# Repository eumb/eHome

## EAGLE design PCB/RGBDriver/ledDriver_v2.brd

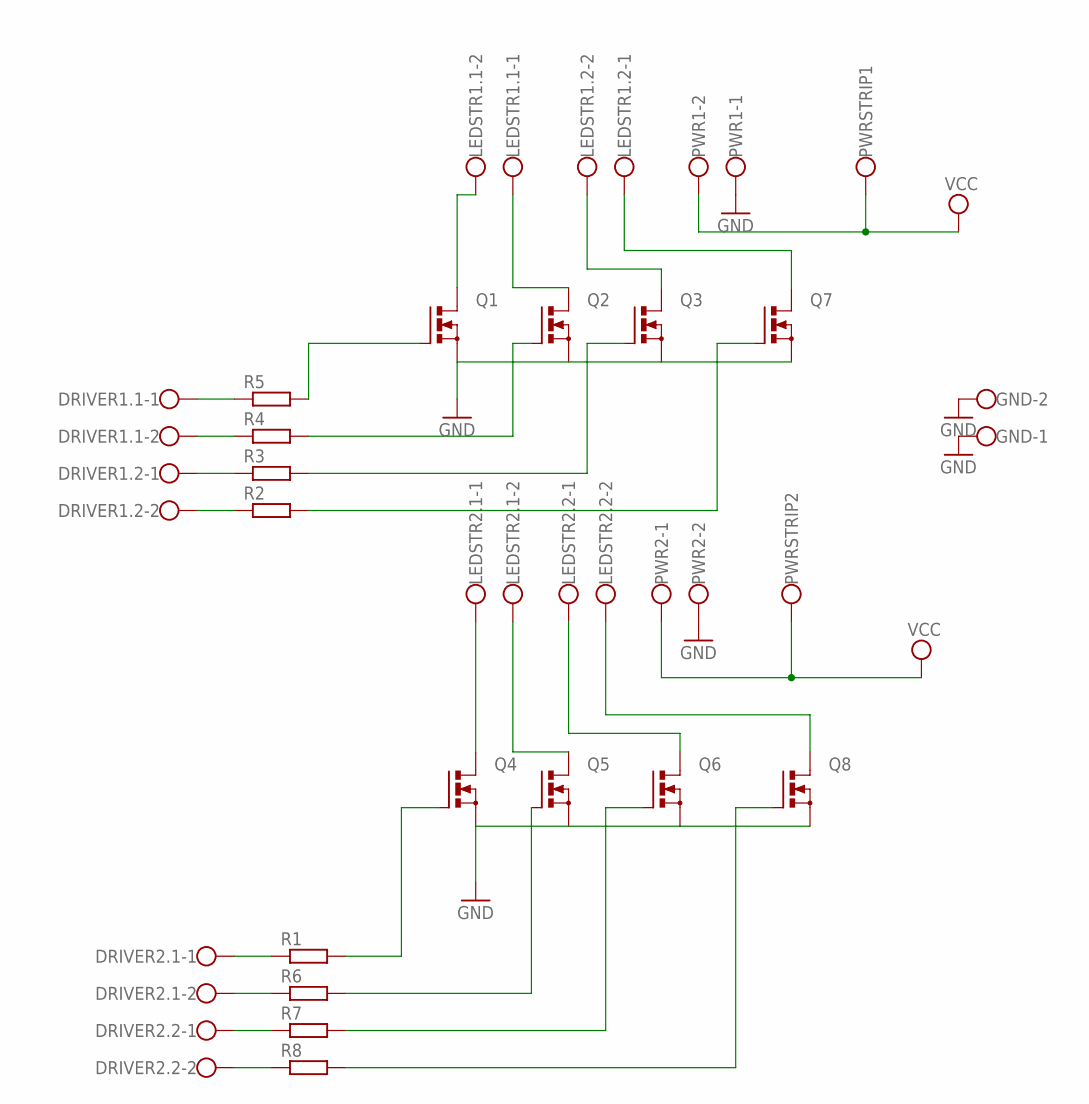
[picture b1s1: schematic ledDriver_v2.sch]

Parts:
DRIVER1.1, DRIVER1.2, DRIVER2.1, DRIVER2.2: W237-102
GND: W237-102
LEDSTR1.1, LEDSTR1.2, LEDSTR2.1, LEDSTR2.2: W237-102
PWR1, PWR2: W237-102
PWRSTRIP1, PWRSTRIP2: W237-112
Q1, Q2, Q3, Q4, Q5, Q6, Q7, Q8: PMOSFET_NTO220BV; TO220BV
R1, R2, R3, R4, R5, R6, R7, R8: R0207/10; 0207/10

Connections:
GND: GND.1, GND.2, PWR1.1, PWR2.2, Q1.S, Q2.S, Q3.S, Q4.S, Q5.S, Q6.S, Q7.S, Q8.S
unnamed: LEDSTR2.1.1, Q4.D
unnamed: LEDSTR2.1.2, Q5.D
unnamed: LEDSTR1.1.2, Q1.D
unnamed: LEDSTR1.1.1, Q2.D
unnamed: LEDSTR1.2.2, Q3.D
unnamed: LEDSTR1.2.1, Q7.D
unnamed: LEDSTR2.2.1, Q6.D
unnamed: LEDSTR2.2.2, Q8.D
unnamed: Q6.G, R7.2
unnamed: Q8.G, R8.2
unnamed: Q1.G, R5.2
unnamed: Q2.G, R4.2
unnamed: Q3.G, R3.2
unnamed: Q7.G, R2.2
unnamed: Q4.G, R1.2
unnamed: Q5.G, R6.2
unnamed: DRIVER1.1.1, R5.1
unnamed: DRIVER1.1.2, R4.1
unnamed: DRIVER1.2.1, R3.1
unnamed: DRIVER1.2.2, R2.1
unnamed: DRIVER2.1.1, R1.1
unnamed: DRIVER2.1.2, R6.1
unnamed: DRIVER2.2.1, R7.1
unnamed: DRIVER2.2.2, R8.1
VCC1: PWR1.2, PWRSTRIP1.1
VCC2: PWR2.1, PWRSTRIP2.1

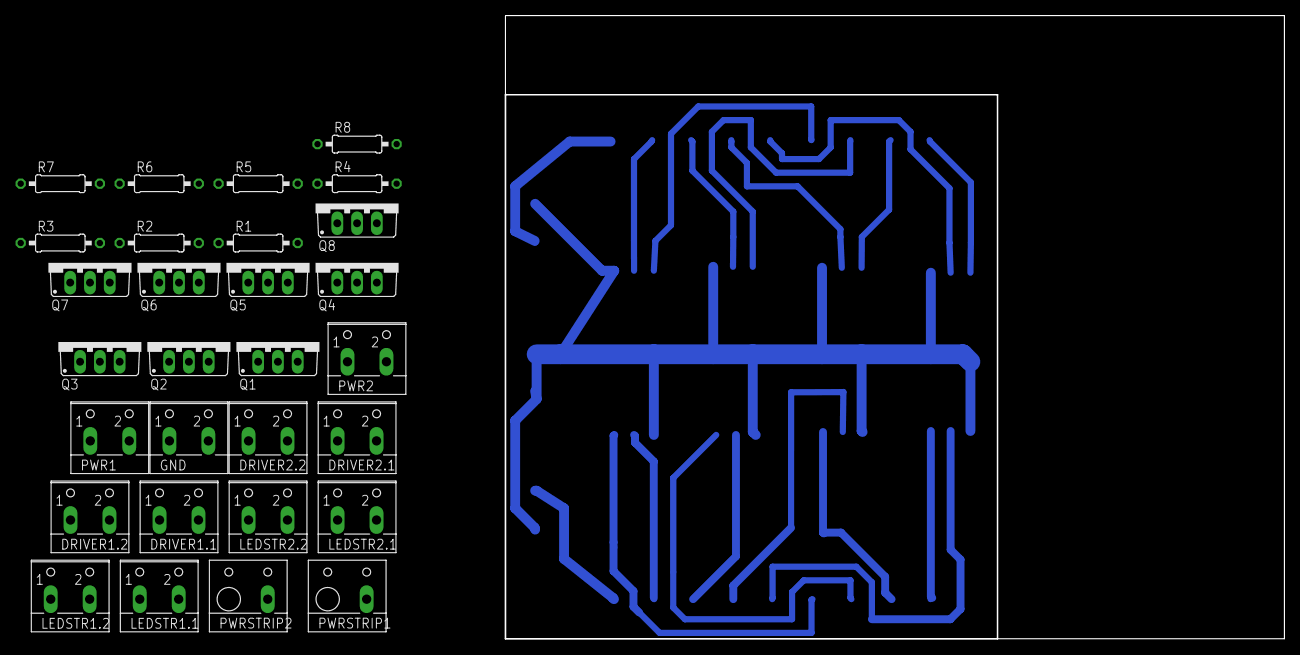
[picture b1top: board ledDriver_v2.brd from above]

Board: 2 copper layers, 100.0 x 80.0 mm, 29 parts (0 on the bottom side), 27 nets.

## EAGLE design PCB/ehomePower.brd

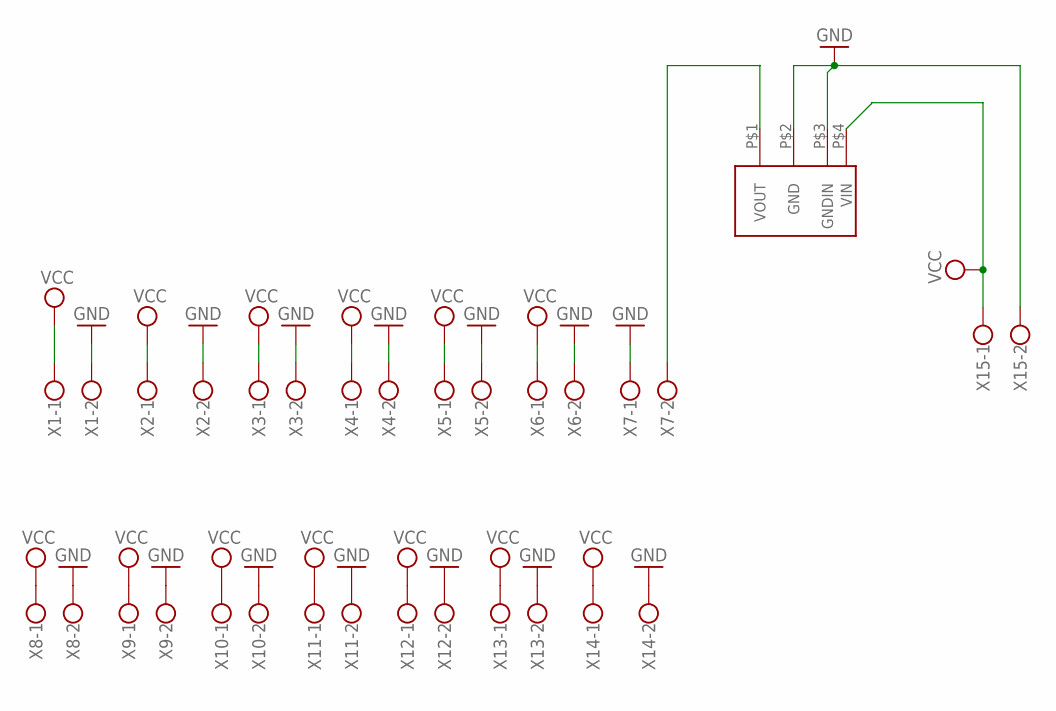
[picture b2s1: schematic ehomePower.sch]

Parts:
U$2: AM2DS
X1, X2, X3, X4, X5, X6, X7, X8, X9, X10, X11, X12, X13, X14, X15: W237-102

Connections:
GND: U$2.P$2 (GND), U$2.P$3 (GNDIN), X1.2, X2.2, X3.2, X4.2, X5.2, X6.2, X7.1, X8.2, X9.2, X10.2, X11.2, X12.2, X13.2, X14.2, X15.2
unnamed: U$2.P$1 (VOUT), X7.2
VCC: U$2.P$4 (VIN), X1.1, X2.1, X3.1, X4.1, X5.1, X6.1, X8.1, X9.1, X10.1, X11.1, X12.1, X13.1, X14.1, X15.1

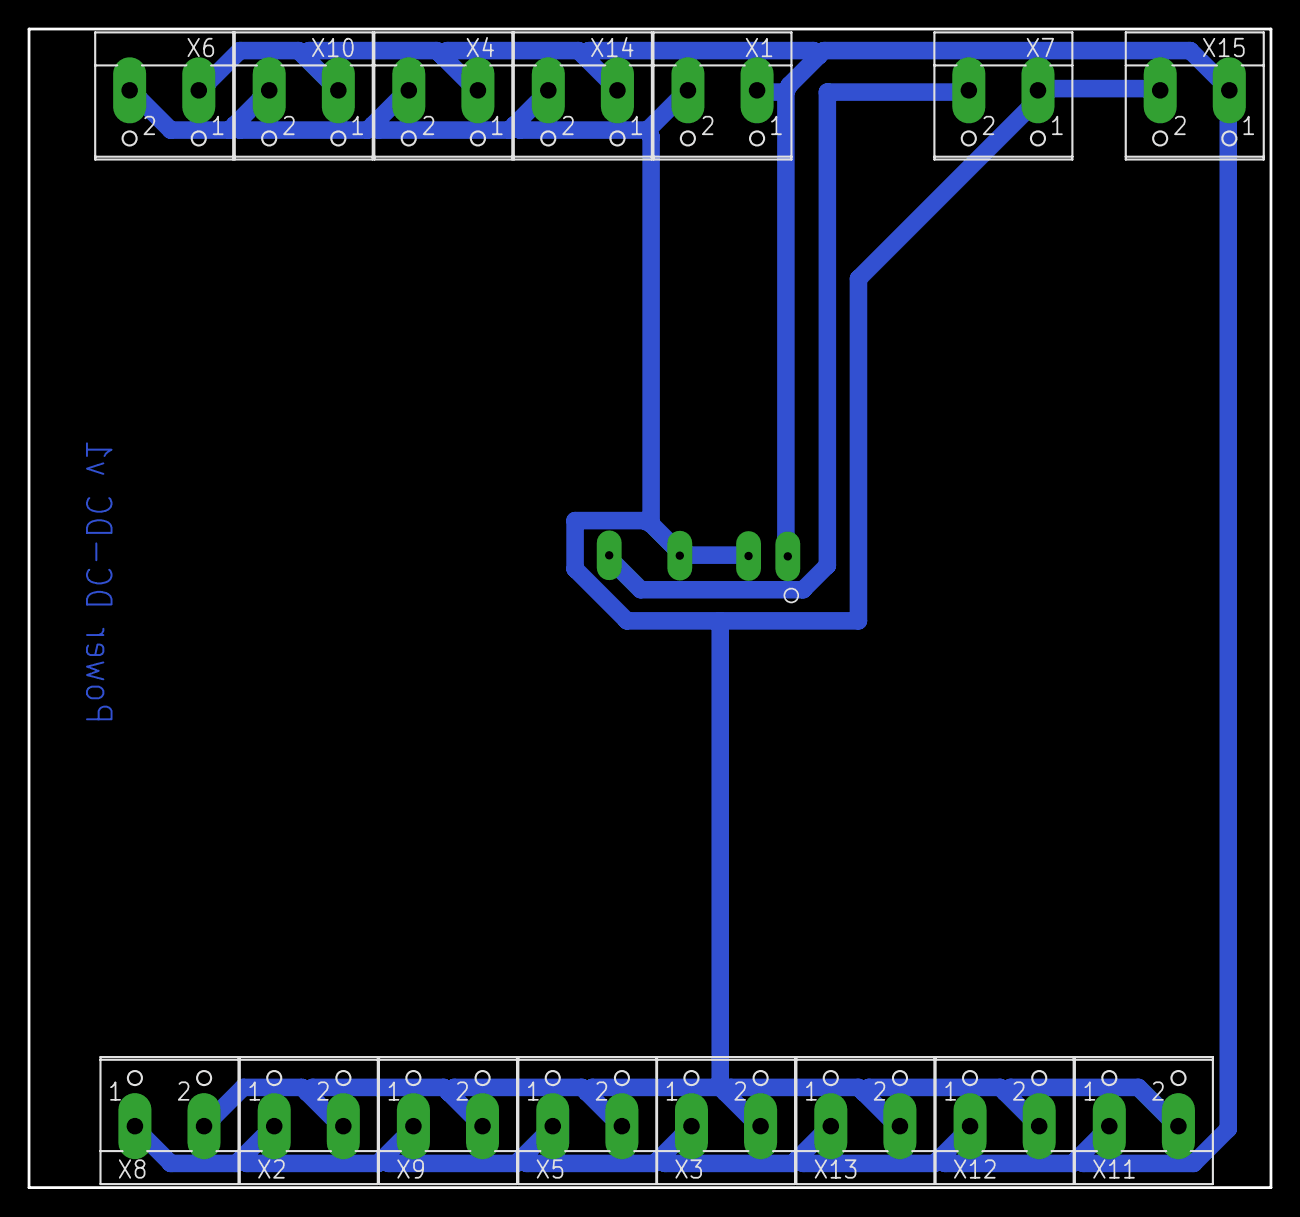
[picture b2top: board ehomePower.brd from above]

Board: 2 copper layers, 89.8 x 83.8 mm, 16 parts (0 on the bottom side), 3 nets.

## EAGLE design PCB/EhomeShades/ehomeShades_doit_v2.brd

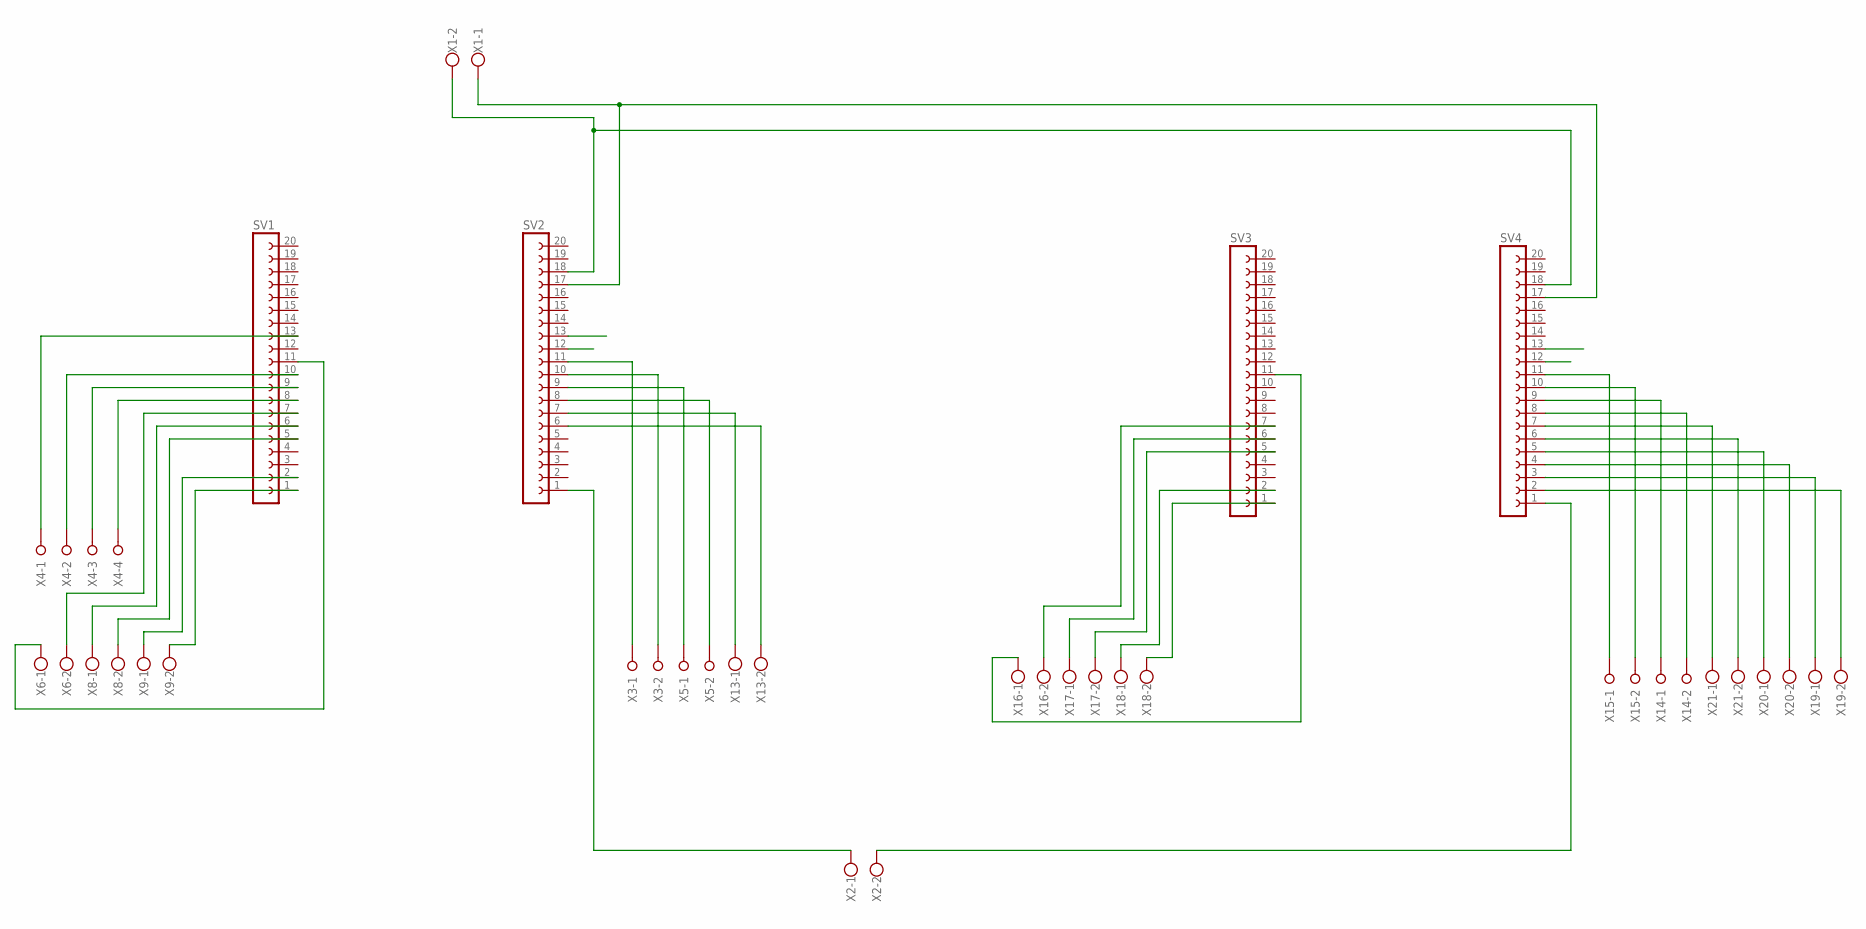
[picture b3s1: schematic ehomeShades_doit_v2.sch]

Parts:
SV1, SV2, SV3, SV4: FE20-1; FE20
X1, X2, X6, X8, X9, X13, X16, X17, X18, X19, X20, X21: W237-102
X3, X5, X14, X15: W237-02P; W237-132
X4: W237-04P; W237-4P

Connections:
EN: SV2.1, X2.1
EN1: SV4.1, X2.2
GND: SV2.17, SV4.17, X1.1
GPIO1: SV4.8, X14.2
GPIO2: SV4.2, X19.2
GPIO3: SV4.3, X19.1
GPIO4: SV1.11, X6.1
GPIO5: SV1.8, X4.4
GPIO6: SV4.4, X20.2
GPIO7: SV4.5, X20.1
GPIO8: SV4.6, X21.2
GPIO9: SV4.7, X21.1
GPIO12: SV2.12
GPIO13: SV2.13
GPIO14: SV2.11, X3.1
GPIO15: SV1.13, X4.1
GPIO16: SV1.10, X4.2
GPIO17: SV1.9, X4.3
GPIO18: SV1.7, X6.2
GPIO19: SV1.6, X8.1
GPIO20: SV3.7, X16.2
GPIO21: SV1.5, X8.2
GPIO22: SV1.2, X9.1
GPIO23: SV1.1, X9.2
GPIO24: SV3.6, X17.1
GPIO25: SV2.8, X5.2
GPIO26: SV2.9, X5.1
GPIO27: SV2.10, X3.2
GPIO28: SV4.9, X14.1
GPIO29: SV4.10, X15.2
GPIO30: SV4.11, X15.1
GPIO31: SV4.13
GPIO32: SV2.6, X13.2
GPIO33: SV2.7, X13.1
GPIO40: SV3.5, X17.2
GPIO41: SV3.2, X18.1
GPIO42: SV3.1, X18.2
GPIO43: SV3.11, X16.1
GPIO44: SV4.12
PWR: SV2.18, SV4.18, X1.2

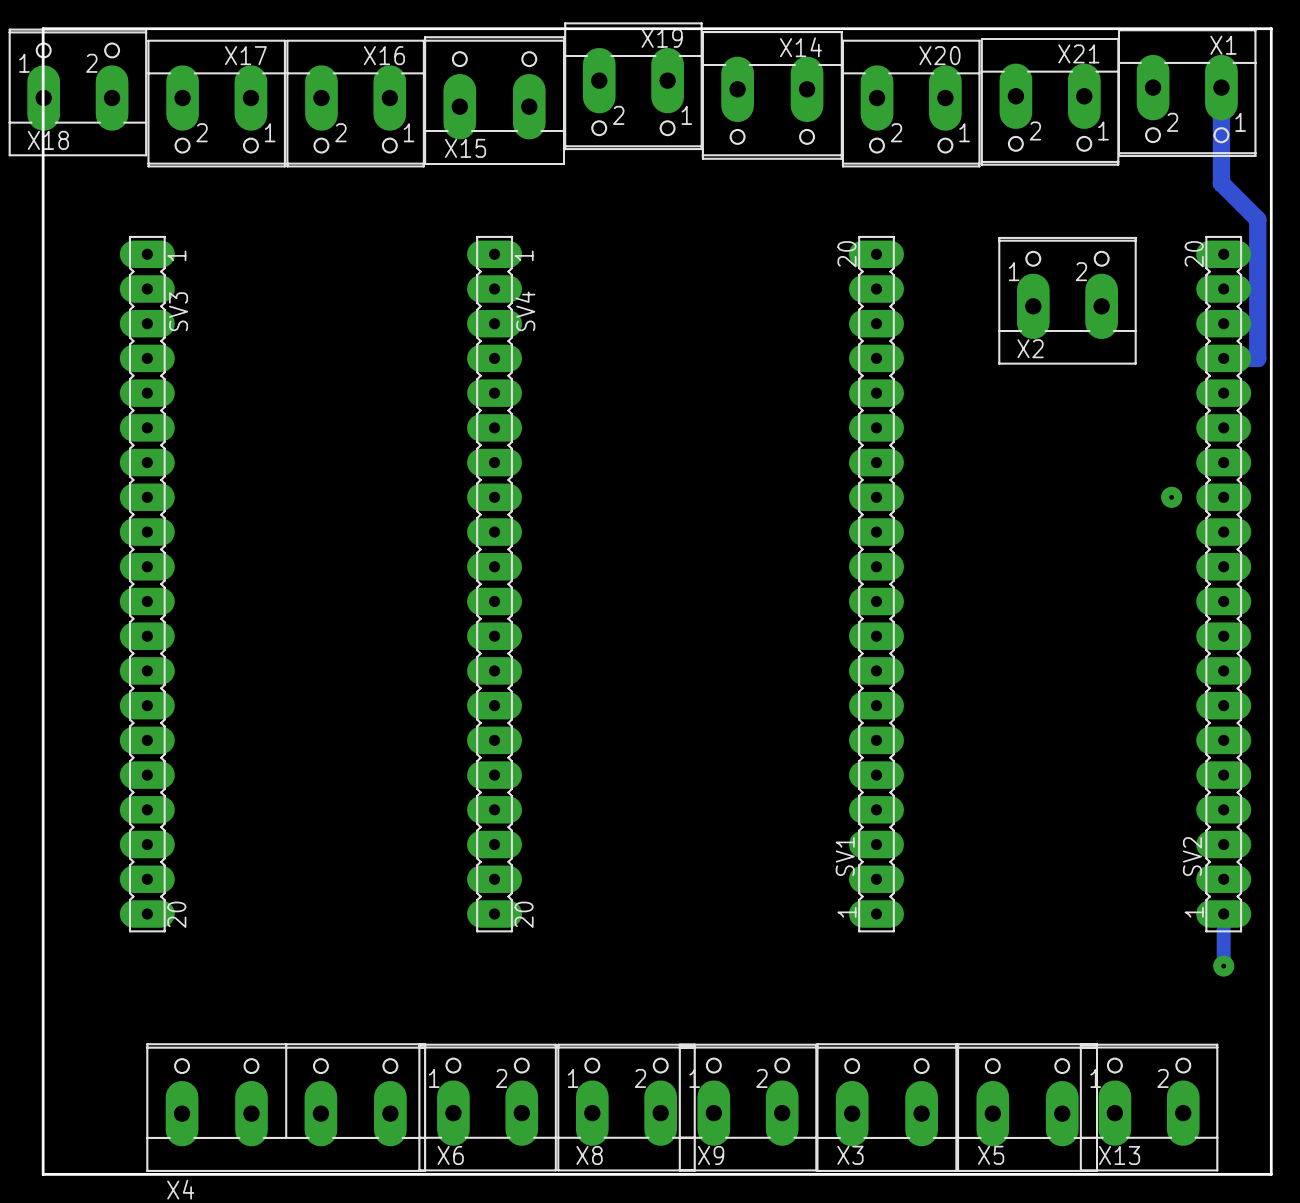
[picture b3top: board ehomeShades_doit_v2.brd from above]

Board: 2 copper layers, 89.8 x 83.8 mm, 21 parts (0 on the bottom side), 36 nets.

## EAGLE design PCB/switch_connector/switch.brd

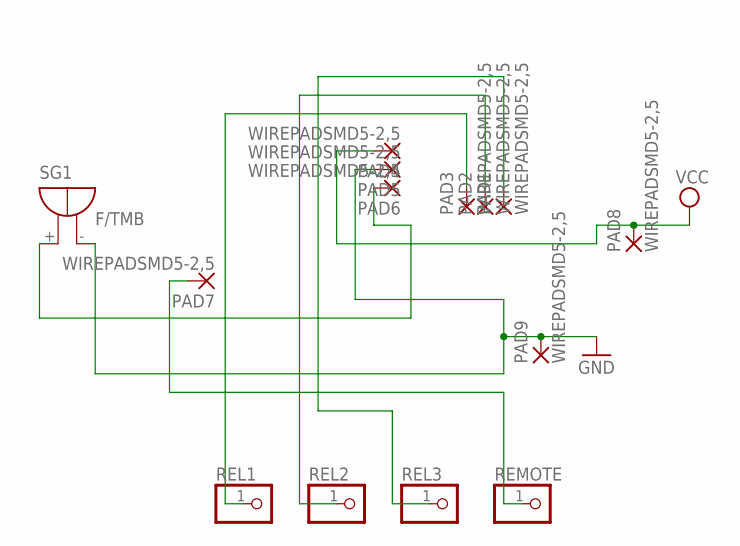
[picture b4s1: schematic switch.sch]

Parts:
PAD1, PAD2, PAD3, PAD4, PAD5, PAD6, PAD7, PAD8, PAD9: WIREPADSMD5-2,5; 5-2,5
REL1, REL2, REL3: PINHD-1X1; 1X01
REMOTE: PINHD-1X1; 1X01
SG1: F/TMB

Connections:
GND: PAD5.1, PAD9.1, SG1.-
unnamed: PAD3.1, REL1.1
unnamed: PAD2.1, REL2.1
unnamed: PAD1.1, REL3.1
unnamed: PAD7.1, REMOTE.1
unnamed: PAD6.1, SG1.+
VCC: PAD4.1, PAD8.1

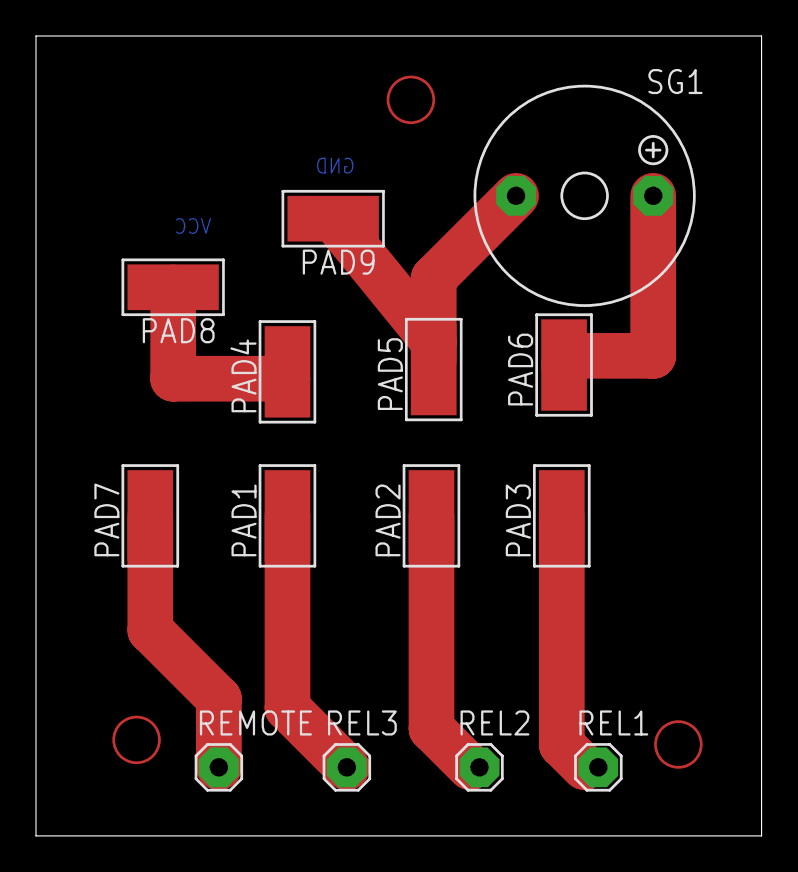
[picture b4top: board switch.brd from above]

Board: 2 copper layers, 40.3 x 44.4 mm, 14 parts (0 on the bottom side), 7 nets.

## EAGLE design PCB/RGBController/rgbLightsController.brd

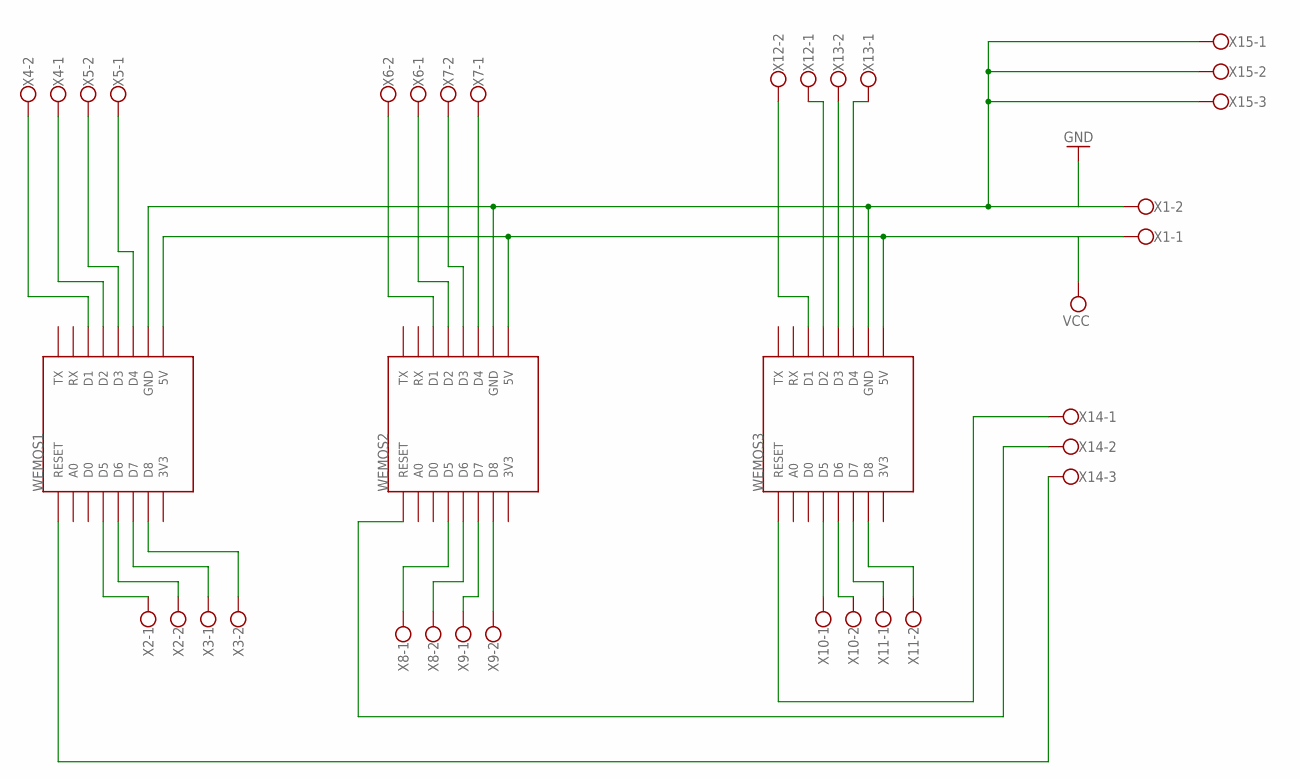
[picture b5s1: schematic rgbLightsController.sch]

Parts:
WEMOS1, WEMOS2, WEMOS3: WEMOS-D1-MINI
X1, X2, X3, X4, X5, X6, X7, X8, X9, X10, X11, X12, X13: W237-102
X14, X15: W237-103

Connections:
GND: WEMOS1.GND, WEMOS2.GND, WEMOS3.GND, X1.2, X15.1, X15.2, X15.3
unnamed: WEMOS2.D1, X6.2
unnamed: WEMOS2.D2, X6.1
unnamed: WEMOS1.D1, X4.2
unnamed: WEMOS1.D2, X4.1
unnamed: WEMOS1.D3, X5.2
unnamed: WEMOS1.D4, X5.1
unnamed: WEMOS2.D3, X7.2
unnamed: WEMOS2.D4, X7.1
unnamed: WEMOS3.D1, X12.2
unnamed: WEMOS3.D2, X12.1
unnamed: WEMOS3.D3, X13.2
unnamed: WEMOS3.D4, X13.1
unnamed: WEMOS1.D5, X2.1
unnamed: WEMOS1.D6, X2.2
unnamed: WEMOS1.D7, X3.1
unnamed: WEMOS1.D8, X3.2
unnamed: WEMOS2.D5, X8.1
unnamed: WEMOS2.D6, X8.2
unnamed: WEMOS2.D7, X9.1
unnamed: WEMOS2.D8, X9.2
unnamed: WEMOS3.D5, X10.1
unnamed: WEMOS3.D6, X10.2
unnamed: WEMOS3.D7, X11.1
unnamed: WEMOS3.D8, X11.2
unnamed: WEMOS2.RESET, X14.2
unnamed: WEMOS1.RESET, X14.3
VCC: WEMOS1.5V, WEMOS2.5V, WEMOS3.5V, X1.1

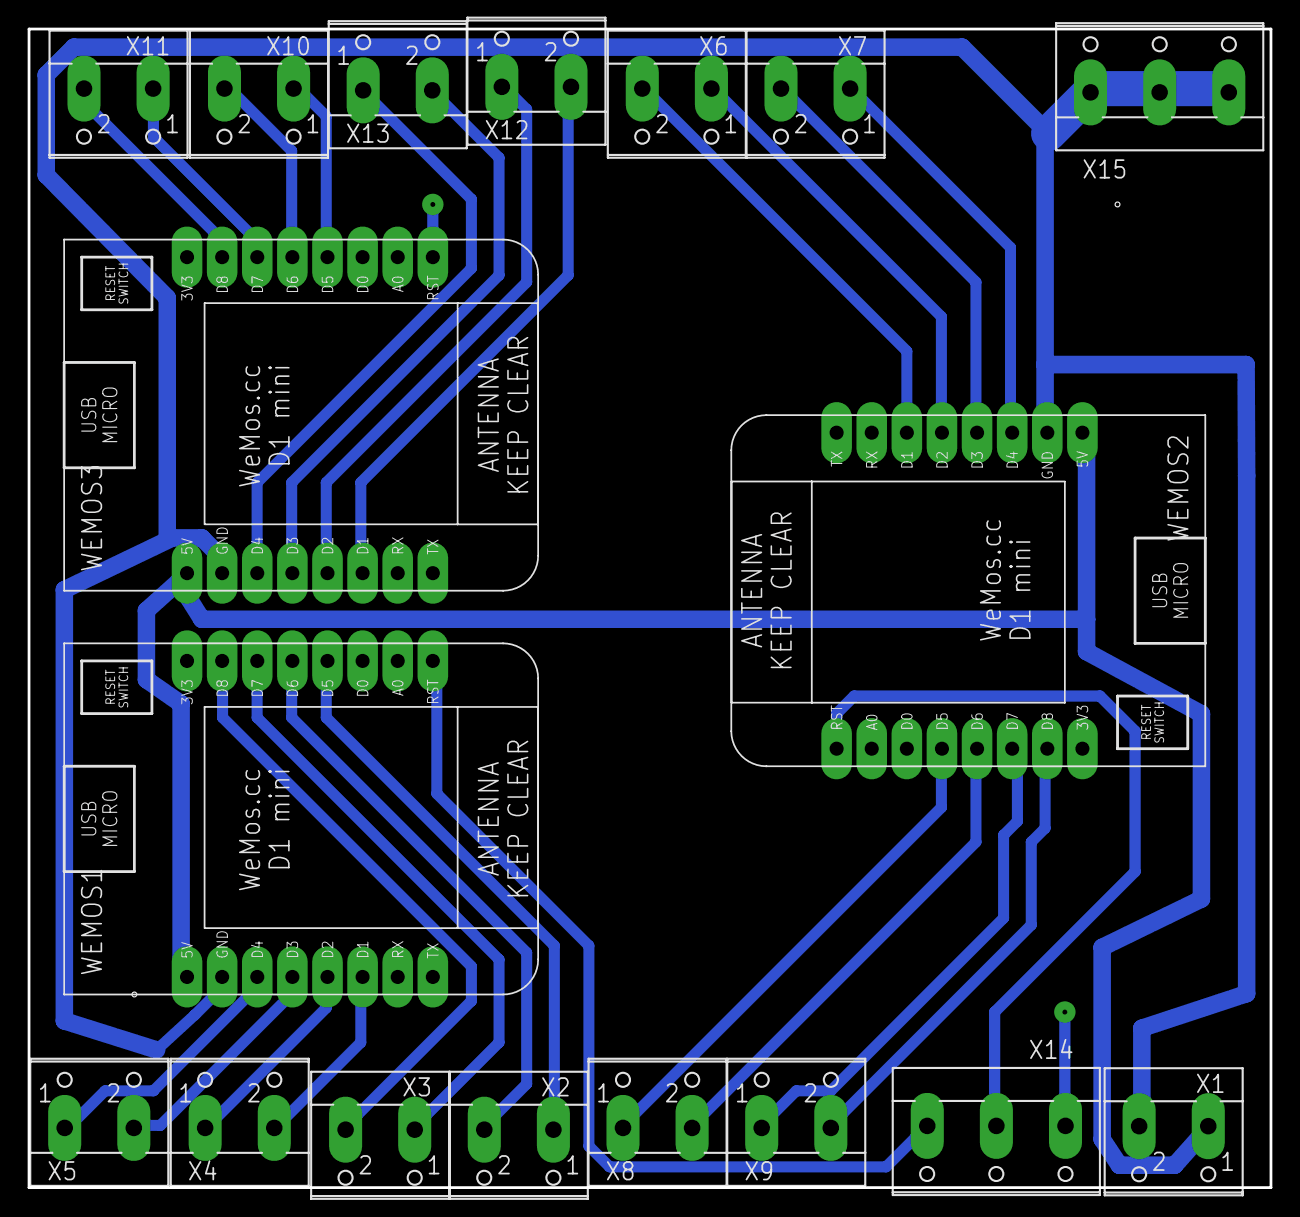
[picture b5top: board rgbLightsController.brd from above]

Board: 2 copper layers, 89.8 x 83.8 mm, 18 parts (0 on the bottom side), 28 nets.

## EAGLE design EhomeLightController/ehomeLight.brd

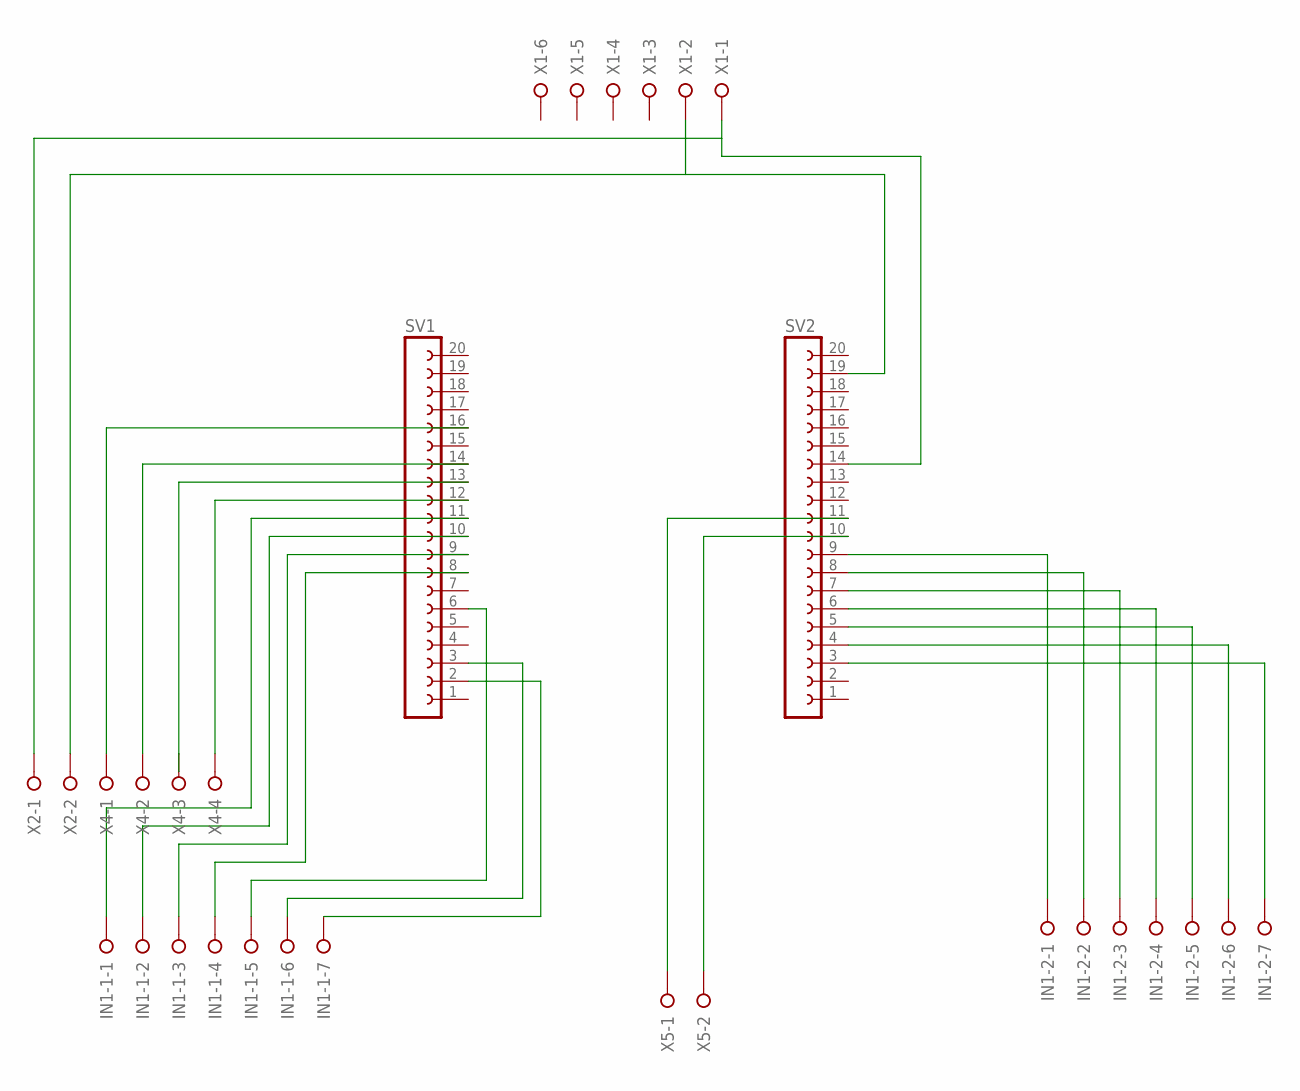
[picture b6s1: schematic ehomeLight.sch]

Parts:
IN1-1, IN1-2: W237-07P; W237-7P
SV1, SV2: FE20-1; FE20
X1: W237-06P; W237-6P
X2, X5: W237-02P; W237-132
X4: W237-04P; W237-4P

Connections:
GND: SV2.14, X1.1, X2.1
GPIO0: SV1.14, X4.2
GPIO4: SV1.13, X4.3
GPIO5: IN1-1.2, SV1.10
GPIO15: SV1.16, X4.1
GPIO16: SV1.12, X4.4
GPIO17: IN1-1.1, SV1.11
GPIO18: IN1-1.3, SV1.9
GPIO19: IN1-1.4, SV1.8
GPIO21: IN1-1.5, SV1.6
GPIO22: IN1-1.6, SV1.3
GPIO23: IN1-1.7, SV1.2
GPIO25: IN1-2.1, SV2.9
GPIO26: SV2.10, X5.2
GPIO27: SV2.11, X5.1
GPIO32: IN1-2.3, SV2.7
GPIO33: IN1-2.2, SV2.8
GPIO34: IN1-2.5, SV2.5
GPIO35: IN1-2.4, SV2.6
GPIO36: IN1-2.7, SV2.3
GPIO39: IN1-2.6, SV2.4
PWR: SV2.19, X1.2, X2.2

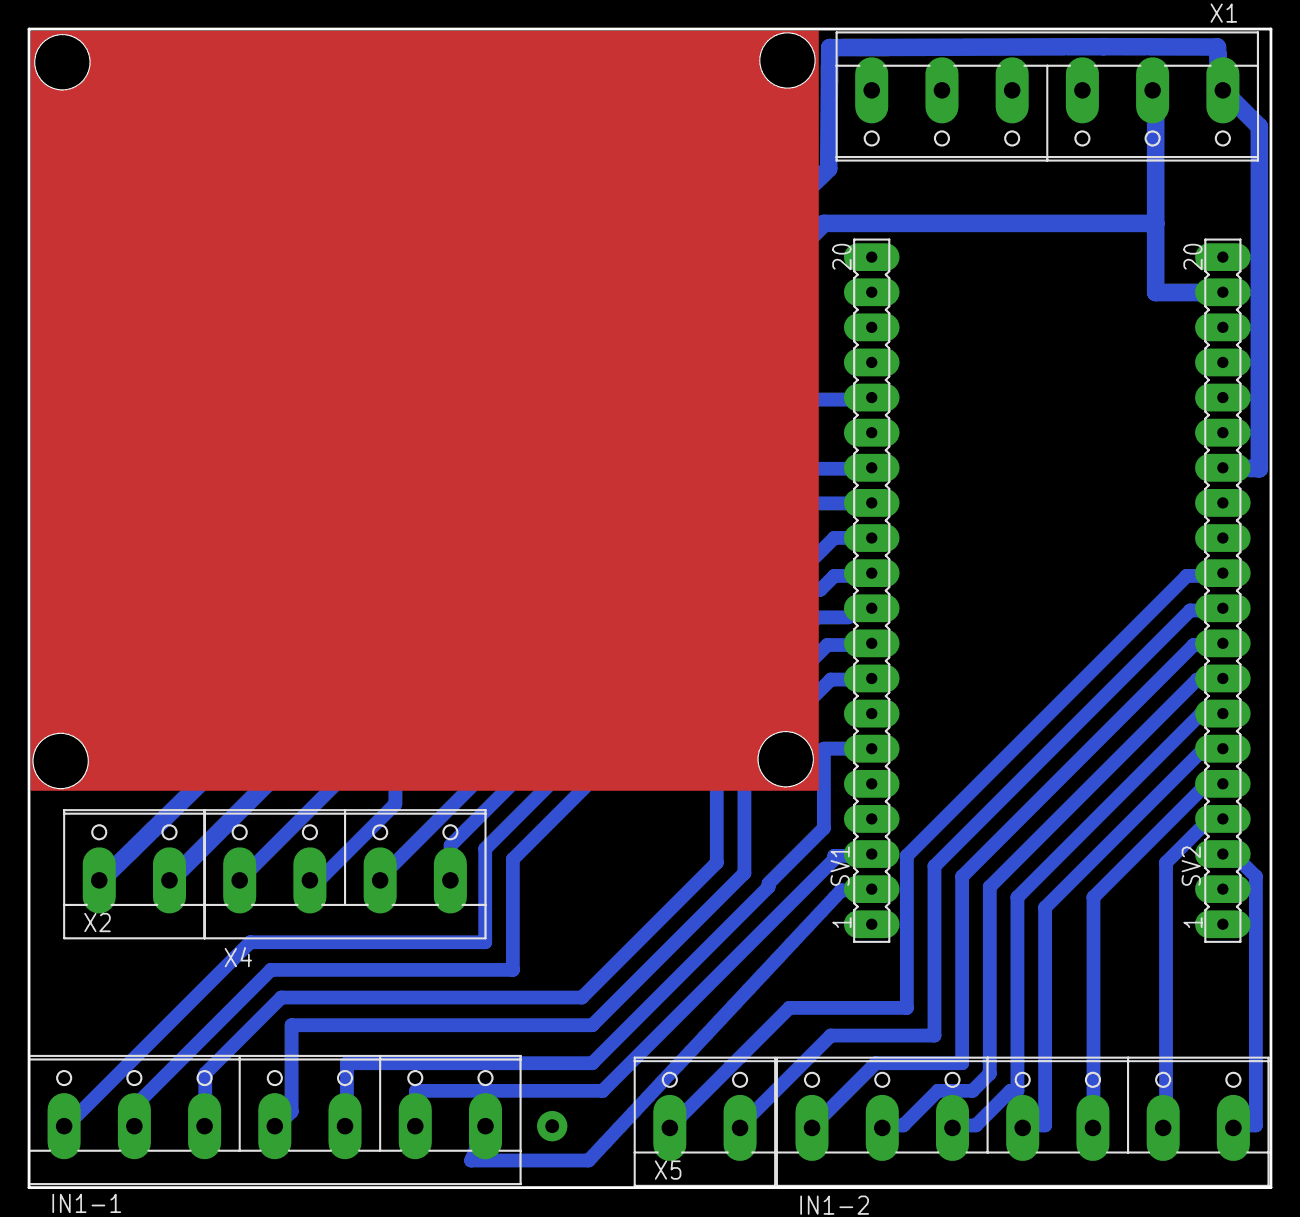
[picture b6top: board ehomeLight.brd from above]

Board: 2 copper layers, 89.8 x 83.8 mm, 8 parts (0 on the bottom side), 22 nets.

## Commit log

2018-03-06 v1.0
2018-03-07 adding schematics and dashboard
2018-03-07 remove junk
2018-03-07 adding led driver
2018-03-16 changes to ehomeGW
2018-03-16 Auto stash before merge of "master" and "origin/master"
2018-03-16 adding backup and changes to ehomegw
2018-03-21 mikrotik connection
2018-03-25 adding SwUnit
2018-05-02 new versions
2018-05-02 cleaning
2018-05-02 all files
2018-05-17 Last changes
2018-07-03 latest and greatest
2018-08-17 all devices on ground floor
